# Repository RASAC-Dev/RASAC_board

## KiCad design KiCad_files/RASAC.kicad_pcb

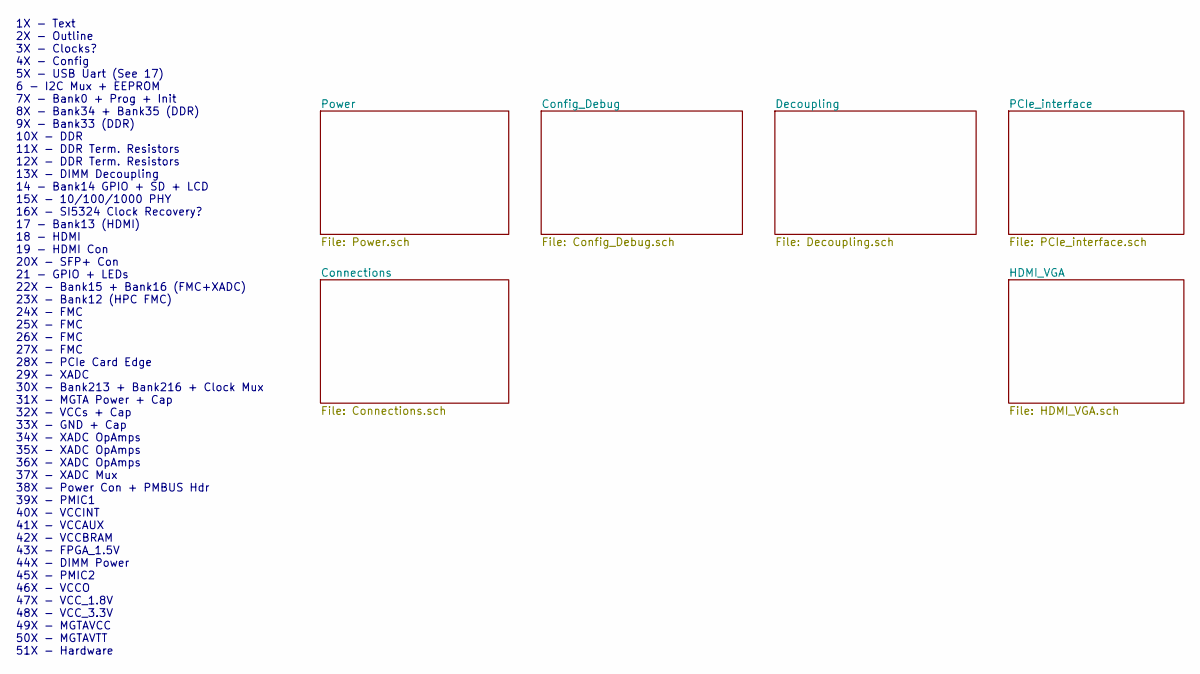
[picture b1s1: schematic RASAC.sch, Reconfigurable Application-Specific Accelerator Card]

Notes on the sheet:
1X - Text 2X - Outline 3X - Clocks? 4X - Config 5X - USB Uart (See 17) 6 - I2C Mux + EEPROM 7X - Bank0 + Prog + Init 8X - Bank34 + Bank35 (DDR) 9X - Bank33 (DDR) 10X - DDR 11X - DDR Term. Resistors 12X - DDR Term. Resistors 13X - DIMM Decoupling 14 - Bank14 GPIO + SD + LCD 15X - 10/100/1000 PHY 16X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

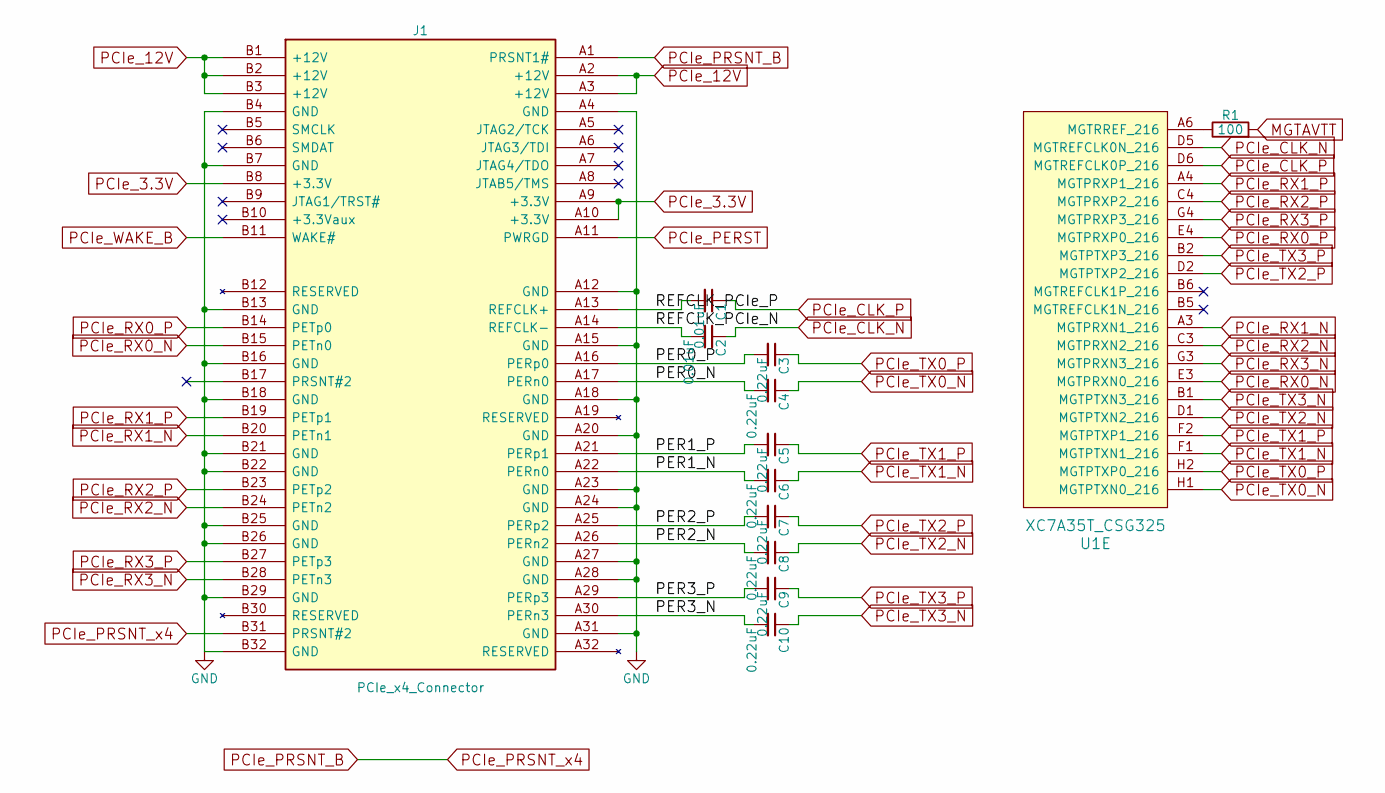
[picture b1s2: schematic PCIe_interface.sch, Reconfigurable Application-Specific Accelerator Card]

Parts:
C1, C2: 0.01uF; C_1206
C3, C4, C5, C6, C7, C8, C9, C10: 0.22uF; C_0805
J1: PCIe_x4_Connector; pciex4fingers
R1: 100; R_0603
U1: XC7A35T_CSG325; BGA-324_15.0x15.0mm_Layout18x18_P0.8mm_Ball0.5mm_Pad0.4mm_N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

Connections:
/PCIe_interface/PER0_N: C4.2, J1.A17 (PERn0)
/PCIe_interface/PER0_P: C3.2, J1.A16 (PERp0)
/PCIe_interface/PER1_N: C6.2, J1.A22 (PERn0)
/PCIe_interface/PER1_P: C5.2, J1.A21 (PERp1)
/PCIe_interface/PER2_N: C8.2, J1.A26 (PERn2)
/PCIe_interface/PER2_P: C7.2, J1.A25 (PERp2)
/PCIe_interface/PER3_N: C10.2, J1.A30 (PERn3)
/PCIe_interface/PER3_P: C9.2, J1.A29 (PERp3)
/PCIe_interface/REFCLK_PCIe_N: C2.2, J1.A14 (REFCLK-)
/PCIe_interface/REFCLK_PCIe_P: C1.2, J1.A13 (REFCLK+)
GND: J1.A4 (GND), J1.A12 (GND), J1.A15 (GND), J1.A18 (GND), J1.A20 (GND), J1.A23 (GND), J1.A24 (GND), J1.A27 (GND), J1.A28 (GND), J1.A31 (GND), J1.B4 (GND), J1.B7 (GND), J1.B13 (GND), J1.B16 (GND), J1.B18 (GND), J1.B21 (GND), J1.B22 (GND), J1.B25 (GND), J1.B26 (GND), J1.B29 (GND), J1.B32 (GND); also elsewhere on the board
MGTAVTT: R1.2; also elsewhere on the board
unnamed: R1.1, U1.A6 (MGTRREF_216)
PCIe_3.3V: J1.A9 (+3.3V), J1.A10 (+3.3V), J1.B8 (+3.3V); also elsewhere on the board
PCIe_12V: J1.A2 (+12V), J1.A3 (+12V), J1.B1 (+12V), J1.B2 (+12V), J1.B3 (+12V); also elsewhere on the board
PCIe_CLK_N: C2.1, U1.D5 (MGTREFCLK0N_216)
PCIe_CLK_P: C1.1, U1.D6 (MGTREFCLK0P_216)
PCIe_PERST: J1.A11 (PWRGD); also elsewhere on the board
PCIe_PRSNT_B: J1.A1 (PRSNT1#), J1.B31 (PRSNT#2)
PCIe_RX0_N: J1.B15 (PETn0), U1.E3 (MGTPRXN0_216)
PCIe_RX0_P: J1.B14 (PETp0), U1.E4 (MGTPRXP0_216)
PCIe_RX1_N: J1.B20 (PETn1), U1.A3 (MGTPRXN1_216)
PCIe_RX1_P: J1.B19 (PETp1), U1.A4 (MGTPRXP1_216)
PCIe_RX2_N: J1.B24 (PETn2), U1.C3 (MGTPRXN2_216)
PCIe_RX2_P: J1.B23 (PETp2), U1.C4 (MGTPRXP2_216)
PCIe_RX3_N: J1.B28 (PETn3), U1.G3 (MGTPRXN3_216)
PCIe_RX3_P: J1.B27 (PETp3), U1.G4 (MGTPRXP3_216)
PCIe_TX0_N: C4.1, U1.H1 (MGTPTXN0_216)
PCIe_TX0_P: C3.1, U1.H2 (MGTPTXP0_216)
PCIe_TX1_N: C6.1, U1.F1 (MGTPTXN1_216)
PCIe_TX1_P: C5.1, U1.F2 (MGTPTXP1_216)
PCIe_TX2_N: C8.1, U1.D1 (MGTPTXN2_216)
PCIe_TX2_P: C7.1, U1.D2 (MGTPTXP2_216)
PCIe_TX3_N: C10.1, U1.B1 (MGTPTXN3_216)
PCIe_TX3_P: C9.1, U1.B2 (MGTPTXP3_216)
PCIe_WAKE_B: J1.B11 (WAKE#); also elsewhere on the board

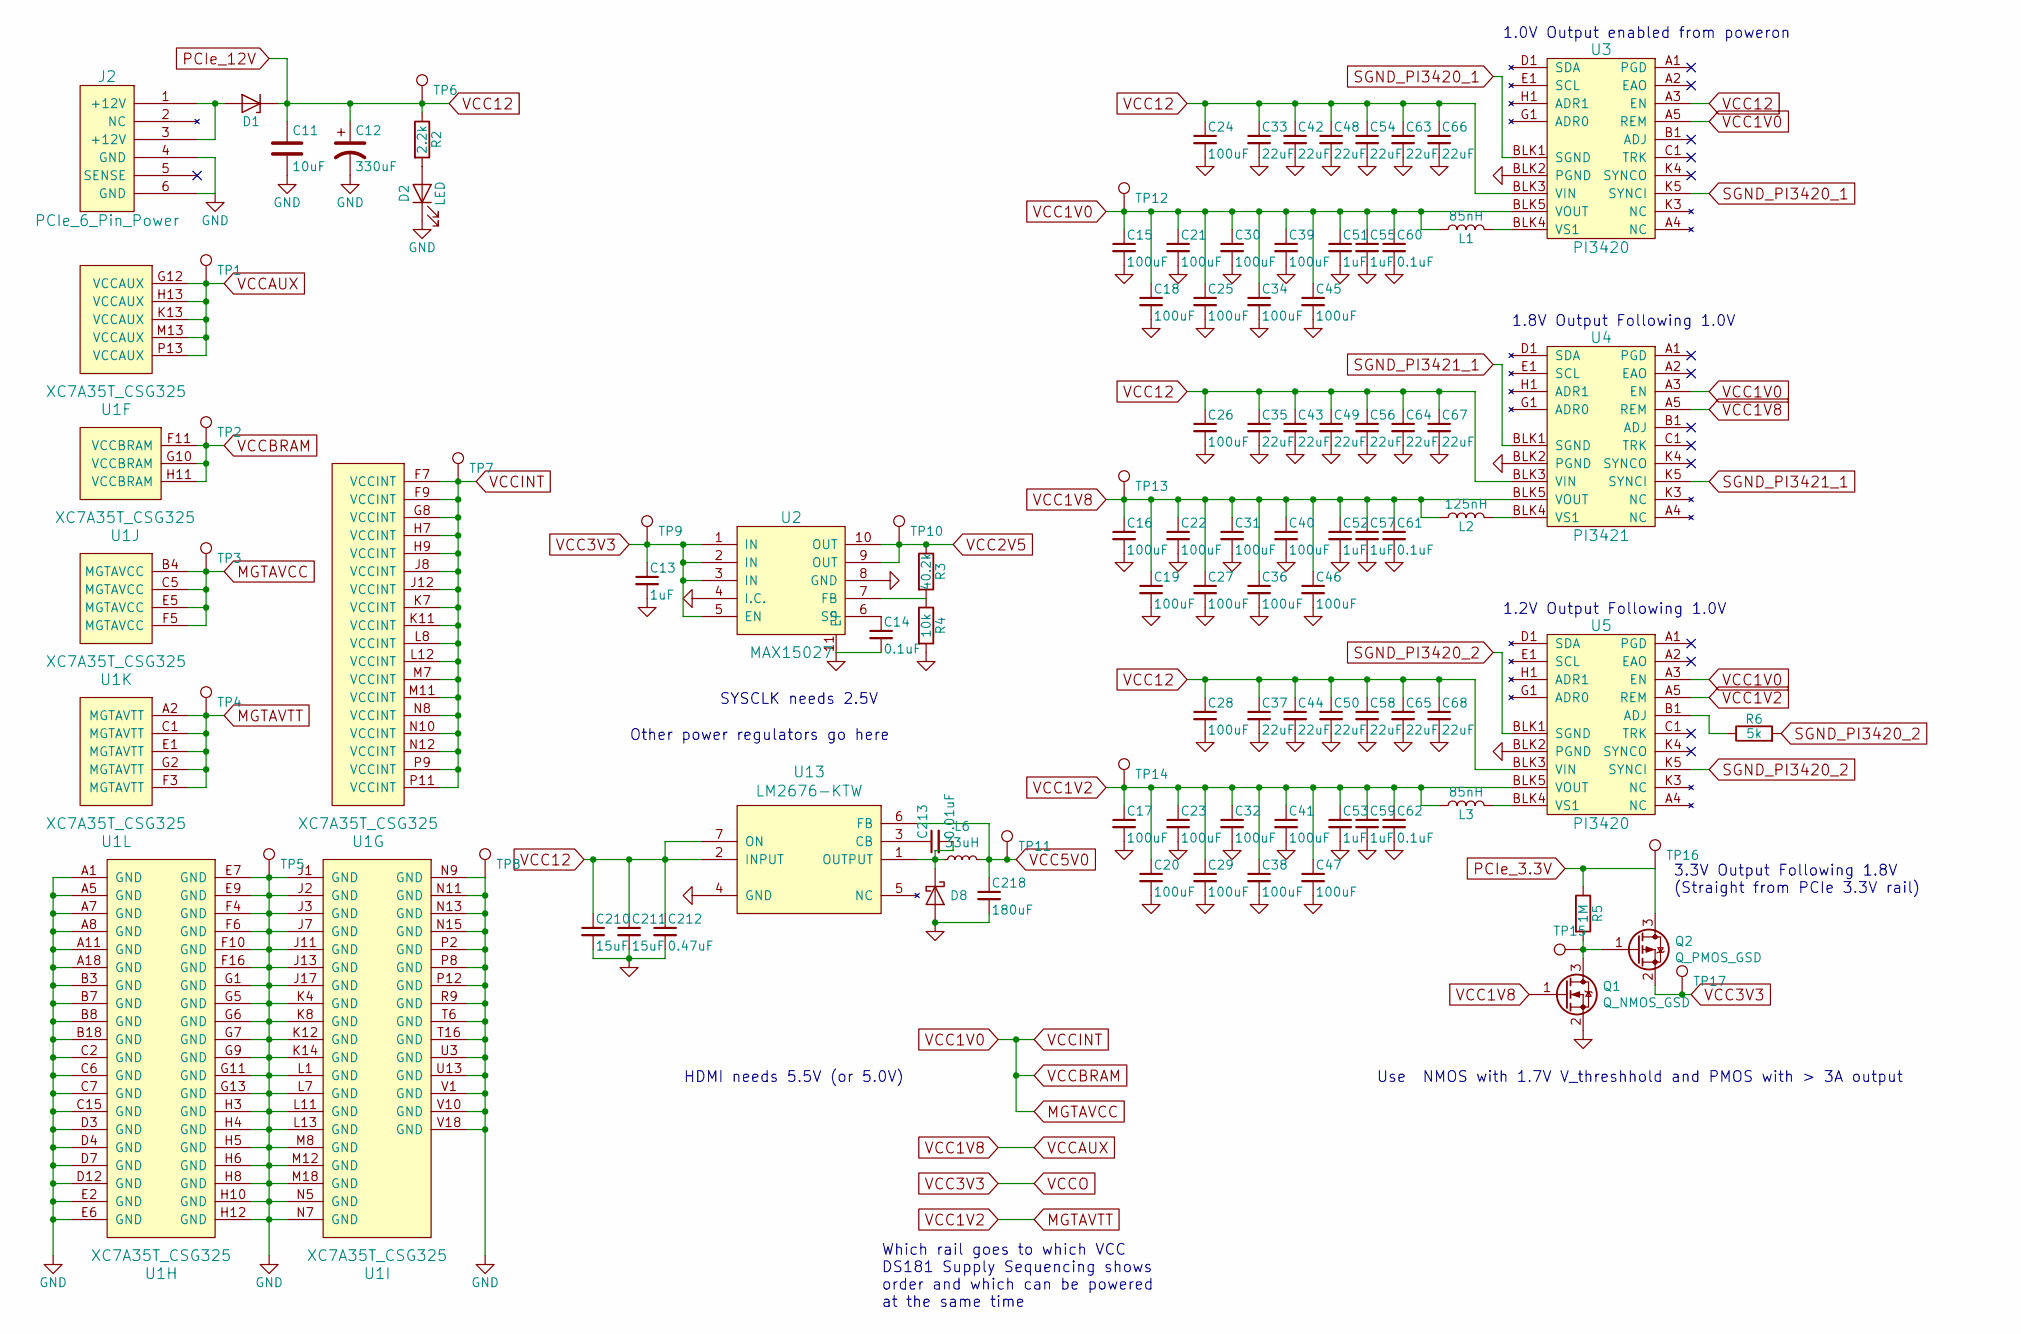
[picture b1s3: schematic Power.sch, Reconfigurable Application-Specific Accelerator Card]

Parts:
C11: 10uF; C_0805
C12: 330uF; C_1210
C13, C51, C52, C53, C55, C57, C59: 1uF; C_0805
C14: 0.1uF; C_0402
C15, C16, C17, C18, C19, C20, C21, C22, C23, C24, C25, C26, C27, C28, C29, C30, C31, C32, C34, C36, C38, C39, C40, C41, C45, C46, C47: 100uF; C_1210
C33, C35, C37, C42, C43, C44, C48, C49, C50, C54, C56, C58, C63, C64, C65, C66, C67, C68: 22uF; C_0805
C60, C61, C62: 0.1uF; C_0805
C210, C211: 15uF; C_1210
C212: 0.47uF; C_0805
C213: 0.01uF; C_1206
C218: 180uF; C_1206
D1: D_Zener; D_SOD-123
D2: LED; LED_0603
D8: D_Schottky; D_SOD-123
J2: PCIe_6_Pin_Power; Molex_MiniFit-JR-5569-06A2_2x03x4.20mm_Angled
L1, L3: 85nH; L_1210
L2: 125nH; L_1210
L6: 33uH; L_0805
Q1: Q_NMOS_GSD; SOT-23
Q2: Q_PMOS_GSD; SOT-23
R2: 2.2k; R_0805
R3: 40.2k; R_0402
R4: 10k; R_0805
R5: 1M; R_0603
R6: 5k; R_0805
TP1, TP2, TP3, TP4, TP5, TP6, TP7, TP8, TP9, TP10, TP11, TP12, TP13, TP14, TP15, TP16, TP17: TestPoint; Measurement_Point_Round-SMD-Pad_Small
U1: XC7A35T_CSG325; BGA-324_15.0x15.0mm_Layout18x18_P0.8mm_Ball0.5mm_Pad0.4mm_N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
U2: MAX15027; TDFN-10_3x3mm_Pitch0.5mm
U3, U5: PI3420; LGA-123_10x14mm_Pitch1.0mm
U4: PI3421; LGA-123_10x14mm_Pitch1.0mm
U13: LM2676-KTW; TO-263-7_TabPin4

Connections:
GND: C11.2, C12.2, C13.2, C14.2, C15.2, C16.2, C17.2, C18.2, C19.2, C20.2, C21.2, C22.2, C23.2, C24.2, C25.2, C26.2, C27.2, C28.2, C29.2, C30.2, C31.2, C32.2, C33.2, C34.2, C35.2, C36.2, C37.2, C38.2, C39.2, C40.2, C41.2, C42.2, C43.2, C44.2, C45.2, C46.2, C47.2, C48.2, C49.2, C50.2, C51.2, C52.2, C53.2, C54.2, C55.2, C56.2, C57.2, C58.2, C59.2, C60.2, C61.2, C62.2, C63.2, C64.2, C65.2, C66.2, C67.2, C68.2, C210.2, C211.2, C212.2, C218.2, D2.1 (K), D8.2 (A), J2.4 (GND), J2.6 (GND), Q1.2 (S), R4.2, TP5.1, TP8.1, U1.A1 (GND), U1.A5 (GND), U1.A7 (GND), U1.A8 (GND), U1.A11 (GND), U1.A18 (GND), U1.B3 (GND), U1.B7 (GND), U1.B8 (GND), U1.B18 (GND), U1.C2 (GND), U1.C6 (GND), U1.C7 (GND), U1.C15 (GND), U1.D3 (GND), U1.D4 (GND), U1.D7 (GND), U1.D12 (GND), U1.E2 (GND), U1.E6 (GND), U1.E7 (GND), U1.E9 (GND), U1.F4 (GND), U1.F6 (GND), U1.F10 (GND), U1.F16 (GND), U1.G1 (GND), U1.G5 (GND), U1.G6 (GND), U1.G7 (GND), U1.G9 (GND), U1.G11 (GND), U1.G13 (GND), U1.H3 (GND), U1.H4 (GND), U1.H5 (GND), U1.H6 (GND), U1.H8 (GND), U1.H10 (GND), U1.H12 (GND), U1.J1 (GND), U1.J2 (GND), U1.J3 (GND), U1.J7 (GND), U1.J11 (GND), U1.J13 (GND), U1.J17 (GND), U1.K4 (GND), U1.K8 (GND), U1.K12 (GND), U1.K14 (GND), U1.L1 (GND), U1.L7 (GND), U1.L11 (GND), U1.L13 (GND), U1.M8 (GND), U1.M12 (GND), U1.M18 (GND), U1.N5 (GND), U1.N7 (GND), U1.N9 (GND), U1.N11 (GND), U1.N13 (GND), U1.N15 (GND), U1.P2 (GND), U1.P8 (GND), U1.P12 (GND), U1.R9 (GND), U1.T6 (GND), U1.T16 (GND), U1.U3 (GND), U1.U13 (GND), U1.V1 (GND), U1.V10 (GND), U1.V18 (GND), U2.4 (I.C.), U2.8 (GND), U2.11 (EP), U3.BLK2 (PGND), U4.BLK2 (PGND), U5.BLK2 (PGND), U13.4 (GND); also elsewhere on the board
MGTAVCC: C15.1, C18.1, C21.1, C25.1, C30.1, C34.1, C39.1, C45.1, C51.1, C55.1, C60.1, L1.1, TP2.1, TP3.1, TP7.1, TP12.1, U1.B4 (MGTAVCC), U1.C5 (MGTAVCC), U1.E5 (MGTAVCC), U1.F5 (MGTAVCC), U1.F7 (VCCINT), U1.F9 (VCCINT), U1.F11 (VCCBRAM), U1.G8 (VCCINT), U1.G10 (VCCBRAM), U1.H7 (VCCINT), U1.H9 (VCCINT), U1.H11 (VCCBRAM), U1.J8 (VCCINT), U1.J12 (VCCINT), U1.K7 (VCCINT), U1.K11 (VCCINT), U1.L8 (VCCINT), U1.L12 (VCCINT), U1.M7 (VCCINT), U1.M11 (VCCINT), U1.N8 (VCCINT), U1.N10 (VCCINT), U1.N12 (VCCINT), U1.P9 (VCCINT), U1.P11 (VCCINT), U3.A5 (REM), U3.BLK5 (VOUT), U4.A3 (EN), U5.A3 (EN); also elsewhere on the board
MGTAVTT: C17.1, C20.1, C23.1, C29.1, C32.1, C38.1, C41.1, C47.1, C53.1, C59.1, C62.1, L3.1, TP4.1, TP14.1, U1.A2 (MGTAVTT), U1.C1 (MGTAVTT), U1.E1 (MGTAVTT), U1.F3 (MGTAVTT), U1.G2 (MGTAVTT), U5.A5 (REM), U5.BLK5 (VOUT); also elsewhere on the board
unnamed: C14.1, U2.6 (SS)
unnamed: C213.1, U13.3 (CB)
unnamed: C213.2, D8.1 (K), L6.1, U13.1 (OUTPUT)
unnamed: D1.2 (A), J2.1 (+12V), J2.3 (+12V)
unnamed: D2.2 (A), R2.2
unnamed: L1.2, U3.BLK4 (VS1)
unnamed: L2.2, U4.BLK4 (VS1)
unnamed: L3.2, U5.BLK4 (VS1)
unnamed: Q1.3 (D), Q2.1 (G), R5.2, TP15.1
unnamed: R3.2, R4.1, U2.7 (FB)
unnamed: R6.1, U5.B1 (ADJ)
PCIe_3.3V: Q2.3 (D), R5.1, TP16.1; also elsewhere on the board
PCIe_12V: C11.1, C12.1, C24.1, C26.1, C28.1, C33.1, C35.1, C37.1, C42.1, C43.1, C44.1, C48.1, C49.1, C50.1, C54.1, C56.1, C58.1, C63.1, C64.1, C65.1, C66.1, C67.1, C68.1, C210.1, C211.1, C212.1, D1.1 (K), R2.1, TP6.1, U3.A3 (EN), U3.BLK3 (VIN), U4.BLK3 (VIN), U5.BLK3 (VIN), U13.2 (INPUT), U13.7 (ON); also elsewhere on the board
SGND_PI3420_1: U3.BLK1 (SGND), U3.K5 (SYNCI)
SGND_PI3420_2: R6.2, U5.BLK1 (SGND), U5.K5 (SYNCI)
SGND_PI3421_1: U4.BLK1 (SGND), U4.K5 (SYNCI)
VCC1V8: C16.1, C19.1, C22.1, C27.1, C31.1, C36.1, C40.1, C46.1, C52.1, C57.1, C61.1, L2.1, Q1.1 (G), TP1.1, TP13.1, U1.G12 (VCCAUX), U1.H13 (VCCAUX), U1.K13 (VCCAUX), U1.M13 (VCCAUX), U1.P13 (VCCAUX), U4.A5 (REM), U4.BLK5 (VOUT); also elsewhere on the board
VCC2V5: R3.1, TP10.1, U2.9 (OUT), U2.10 (OUT); also elsewhere on the board
VCC3V3: C13.1, Q2.2 (S), TP9.1, TP17.1, U2.1 (IN), U2.2 (IN), U2.3 (IN), U2.5 (EN); also elsewhere on the board
VCC5V0: C218.1, L6.2, TP11.1, U13.6 (FB); also elsewhere on the board

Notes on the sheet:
Use NMOS with 1.7V V_threshhold and PMOS with > 3A output
Other power regulators go here
1.2V Output Following 1.0V
1.8V Output Following 1.0V
1.0V Output enabled from poweron
3.3V Output Following 1.8V (Straight from PCIe 3.3V rail)
Which rail goes to which VCC DS181 Supply Sequencing shows order and which can be powered at the same time
SYSCLK needs 2.5V
HDMI needs 5.5V (or 5.0V)

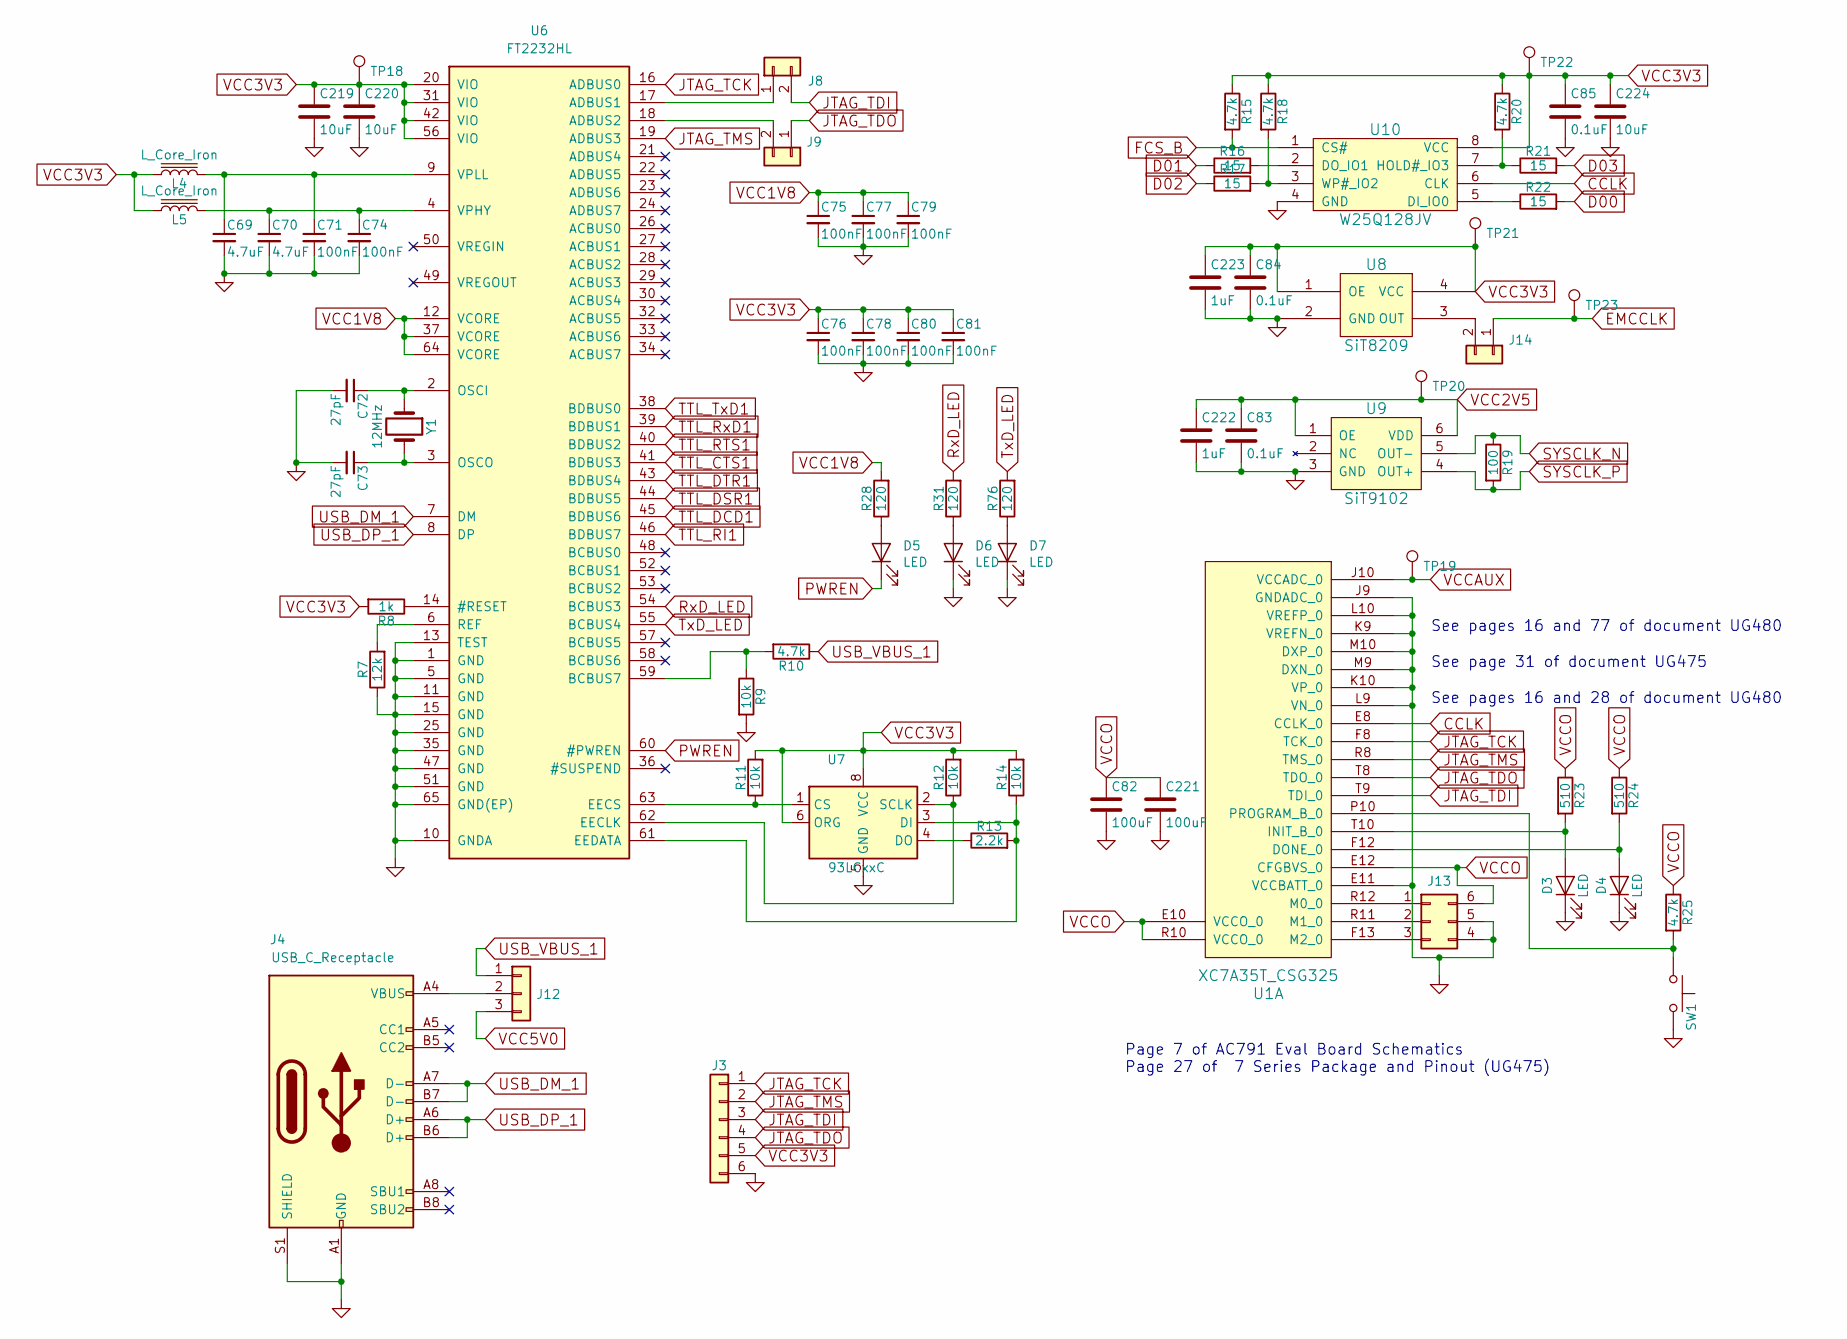
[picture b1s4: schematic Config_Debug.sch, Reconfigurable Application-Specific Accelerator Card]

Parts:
C69, C70: 4.7uF; C_0603
C71, C74, C75, C76, C77, C78, C79, C80, C81: 100nF; C_0805
C72, C73: 27pF; C_0805
C82: 100uF; C_0805
C83, C84, C85: 0.1uF; C_0805
C219, C220, C224: 10uF; C_0805
C221: 100uF; C_1210
C222, C223: 1uF; C_0805
D3, D4, D5, D6, D7: LED; LED_0603
J3: Conn_01x06; Pin_Header_Straight_2x03_Pitch2.54mm
J4: USB_C_Receptacle; USB_C_Receptacle_Amphenol_12401610E4-2A
J8, J9, J14: Conn_01x02; Pin_Header_Straight_1x02_Pitch2.54mm
J12: Conn_01x03; Pin_Header_Straight_1x03_Pitch2.54mm
J13: Conn_02x03_Counter_Clockwise; Pin_Header_Straight_2x03_Pitch2.54mm_SMD
L4, L5: L_Core_Iron; L_0805
R7: 12k; R_0402
R8: 1k; R_0805
R9, R11, R12, R14: 10k; R_0805
R10, R15, R18, R20, R25: 4.7k; R_0805
R13: 2.2k; R_0805
R16, R17, R21, R22: 15; R_0805
R19: 100; R_0603
R23, R24: 510; R_0805
R28, R31, R76: 120; R_0805
SW1: SW_Push; SW_SPST_PTS645
TP18, TP19, TP20, TP21, TP22, TP23: TestPoint; Measurement_Point_Round-SMD-Pad_Small
U1: XC7A35T_CSG325; BGA-324_15.0x15.0mm_Layout18x18_P0.8mm_Ball0.5mm_Pad0.4mm_N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
U6: FT2232HL; LQFP-64-1EP_10x10mm_Pitch0.5mm; MPN FT2232HL
U7: 93LCxxC; SOIC-8-N
U8: SiT8209; 4-SMD
U9: SiT9102; 6-SMD
U10: W25Q128JV; SOIC-8-N
Y1: 12MHz; Crystal_SMD_HC49-SD

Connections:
CCLK: U1.E8 (CCLK_0), U10.6 (CLK)
D00: R22.2; also elsewhere on the board
D01: R16.1; also elsewhere on the board
D02: R17.1; also elsewhere on the board
D03: R21.2; also elsewhere on the board
EMCCLK: J14.1, TP23.1; also elsewhere on the board
FCS_B: R15.2, U10.1 (CS#); also elsewhere on the board
GND: C69.2, C70.2, C71.2, C72.2, C73.2, C74.2, C75.2, C76.2, C77.2, C78.2, C79.2, C80.2, C81.2, C82.2, C83.2, C84.2, C85.2, C219.2, C220.2, C221.2, C222.2, C223.2, C224.2, D3.1 (K), D4.1 (K), D6.1 (K), D7.1 (K), J3.6, J4.A1 (GND), J4.A12 (GND), J4.B1 (GND), J4.B12 (GND), J4.S1 (SHIELD), J13.4, J13.5, R7.1, R9.2, SW1.2, U1.E11 (VCCBATT_0), U1.J9 (GNDADC_0), U1.K9 (VREFN_0), U1.K10 (VP_0), U1.L9 (VN_0), U1.L10 (VREFP_0), U1.M9 (DXN_0), U1.M10 (DXP_0), U6.1 (GND), U6.5 (GND), U6.10 (GNDA), U6.11 (GND), U6.13 (TEST), U6.15 (GND), U6.25 (GND), U6.35 (GND), U6.47 (GND), U6.51 (GND), U6.65 (GND(EP)), U7.5 (GND), U8.2 (GND), U9.3 (GND), U10.4 (GND); also elsewhere on the board
JTAG_TCK: J3.1, U1.F8 (TCK_0), U6.16 (ADBUS0)
JTAG_TDI: J3.3, J8.2, U1.T9 (TDI_0)
JTAG_TDO: J3.4, J9.1, U1.T8 (TDO_0)
JTAG_TMS: J3.2, U1.R8 (TMS_0), U6.19 (ADBUS3)
unnamed: C69.1, C71.1, L4.2, U6.9 (VPLL)
unnamed: C70.1, C74.1, L5.2, U6.4 (VPHY)
unnamed: C72.1, U6.2 (OSCI), Y1.1
unnamed: C73.1, U6.3 (OSCO), Y1.2
unnamed: D3.2 (A), R23.2, U1.T10 (INIT_B_0)
unnamed: D4.2 (A), R24.2, U1.F12 (DONE_0)
unnamed: D5.2 (A), R28.1
unnamed: D6.2 (A), R31.1
unnamed: D7.2 (A), R76.1
unnamed: J8.1, U6.17 (ADBUS1)
unnamed: J9.2, U6.18 (ADBUS2)
unnamed: J4.A4 (VBUS), J4.A9 (VBUS), J4.B4 (VBUS), J4.B9 (VBUS), J12.2
unnamed: J13.1, U1.R12 (M0_0)
unnamed: J13.2, U1.R11 (M1_0)
unnamed: J13.3, U1.F13 (M2_0)
unnamed: J14.2, U8.3 (OUT)
unnamed: R7.2, U6.6 (REF)
unnamed: R8.1, U6.14 (#RESET)
unnamed: R9.1, R10.2, U6.59 (BCBUS7)
unnamed: R11.1, U6.63 (EECS), U7.1 (CS)
unnamed: R12.1, U6.62 (EECLK), U7.2 (SCLK)
unnamed: R13.1, U7.4 (DO)
unnamed: R13.2, R14.1, U6.61 (EEDATA), U7.3 (DI)
unnamed: R16.2, U10.2 (DO_IO1)
unnamed: R17.2, R18.2, U10.3 (WP#_IO2)
unnamed: R20.2, R21.1, U10.7 (HOLD#_IO3)
unnamed: R22.1, U10.5 (DI_IO0)
unnamed: R25.2, SW1.1, U1.P10 (PROGRAM_B_0)
PWREN: D5.1 (K), U6.60 (#PWREN)
RxD_LED: R31.2, U6.54 (BCBUS3)
SYSCLK_N: R19.1, U9.5 (OUT-); also elsewhere on the board
SYSCLK_P: R19.2, U9.4 (OUT+); also elsewhere on the board
TTL_CTS1: U6.41 (BDBUS3); also elsewhere on the board
TTL_DCD1: U6.45 (BDBUS6); also elsewhere on the board
TTL_DSR1: U6.44 (BDBUS5); also elsewhere on the board
TTL_DTR1: U6.43 (BDBUS4); also elsewhere on the board
TTL_RI1: U6.46 (BDBUS7); also elsewhere on the board
TTL_RTS1: U6.40 (BDBUS2); also elsewhere on the board
TTL_RxD1: U6.39 (BDBUS1); also elsewhere on the board
TTL_TxD1: U6.38 (BDBUS0); also elsewhere on the board
TxD_LED: R76.2, U6.55 (BCBUS4)
USB_DM_1: J4.A7 (D-), J4.B7 (D-), U6.7 (DM)
USB_DP_1: J4.A6 (D+), J4.B6 (D+), U6.8 (DP)
USB_VBUS_1: J12.1, R10.1
VCC1V8: C75.1, C77.1, C79.1, R28.2, TP19.1, U1.J10 (VCCADC_0), U6.12 (VCORE), U6.37 (VCORE), U6.64 (VCORE); also elsewhere on the board
VCC2V5: C83.1, C222.1, TP20.1, U9.1 (OE), U9.6 (VDD); also elsewhere on the board
VCC3V3: C76.1, C78.1, C80.1, C81.1, C82.1, C84.1, C85.1, C219.1, C220.1, C221.1, C223.1, C224.1, J3.5, J13.6, L4.1, L5.1, R8.2, R11.2, R12.2, R14.2, R15.1, R18.1, R20.1, R23.1, R24.1, R25.1, TP18.1, TP21.1, TP22.1, U1.E10 (VCCO_0), U1.E12 (CFGBVS_0), U1.R10 (VCCO_0), U6.20 (VIO), U6.31 (VIO), U6.42 (VIO), U6.56 (VIO), U7.6 (ORG), U7.8 (VCC), U8.1 (OE), U8.4 (VCC), U10.8 (VCC); also elsewhere on the board
VCC5V0: J12.3; also elsewhere on the board

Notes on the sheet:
Page 7 of AC791 Eval Board Schematics Page 27 of 7 Series Package and Pinout (UG475)
See pages 16 and 77 of document UG480
See pages 16 and 28 of document UG480
See page 31 of document UG475

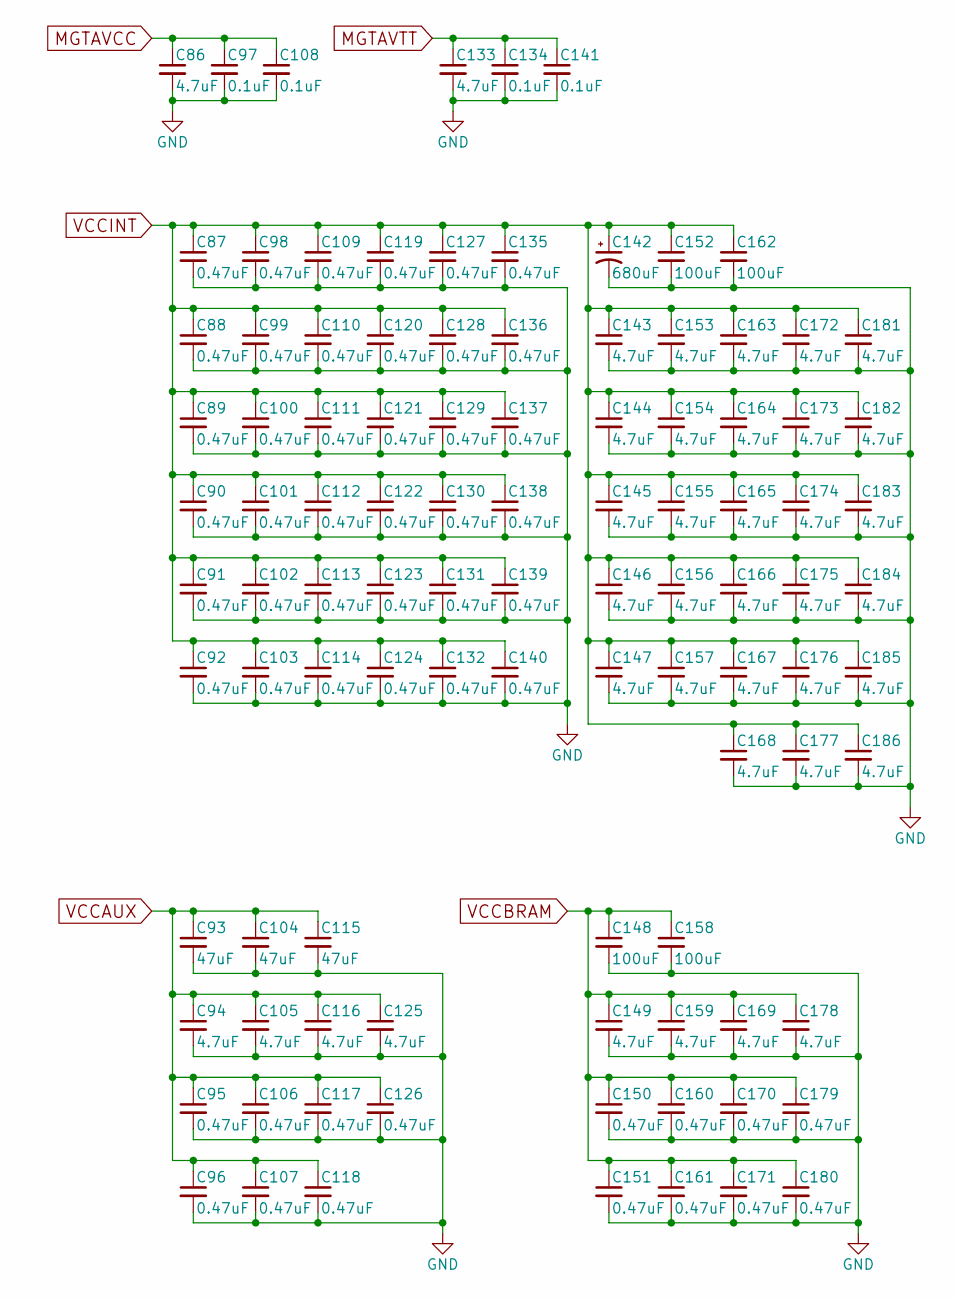
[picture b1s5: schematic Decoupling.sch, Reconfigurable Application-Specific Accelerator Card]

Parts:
C86, C94, C105, C116, C125, C133, C143, C144, C145, C146, C147, C149, C153, C154, C155, C156, C157, C159, C163, C164, C165, C166, C167, C168, C169, C172, C173, C174, C175, C176, C177, C178, C181, C182, C183, C184, C185, C186: 4.7uF; C_0603
C87, C88, C89, C90, C91, C92, C95, C96, C98, C99, C100, C101, C102, C103, C106, C107, C109, C110, C111, C112, C113, C114, C117, C118, C119, C120, C121, C122, C123, C124, C126, C127, C128, C129, C130, C131, C132, C135, C136, C137, C138, C139, C140, C150, C151, C160, C161, C170, C171, C179, C180: 0.47uF; C_0805
C93, C104, C115: 47uF; C_0805
C97, C108, C134, C141: 0.1uF; C_0805
C142: 680uF; CP_Tantalum_Case-D_EIA-7343-31_Wave
C148, C152, C158, C162: 100uF; C_1210

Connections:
GND: C86.2, C87.2, C88.2, C89.2, C90.2, C91.2, C92.2, C93.2, C94.2, C95.2, C96.2, C97.2, C98.2, C99.2, C100.2, C101.2, C102.2, C103.2, C104.2, C105.2, C106.2, C107.2, C108.2, C109.2, C110.2, C111.2, C112.2, C113.2, C114.2, C115.2, C116.2, C117.2, C118.2, C119.2, C120.2, C121.2, C122.2, C123.2, C124.2, C125.2, C126.2, C127.2, C128.2, C129.2, C130.2, C131.2, C132.2, C133.2, C134.2, C135.2, C136.2, C137.2, C138.2, C139.2, C140.2, C141.2, C142.2, C143.2, C144.2, C145.2, C146.2, C147.2, C148.2, C149.2, C150.2, C151.2, C152.2, C153.2, C154.2, C155.2, C156.2, C157.2, C158.2, C159.2, C160.2, C161.2, C162.2, C163.2, C164.2, C165.2, C166.2, C167.2, C168.2, C169.2, C170.2, C171.2, C172.2, C173.2, C174.2, C175.2, C176.2, C177.2, C178.2, C179.2, C180.2, C181.2, C182.2, C183.2, C184.2, C185.2, C186.2; also elsewhere on the board
MGTAVCC: C86.1, C87.1, C88.1, C89.1, C90.1, C91.1, C92.1, C97.1, C98.1, C99.1, C100.1, C101.1, C102.1, C103.1, C108.1, C109.1, C110.1, C111.1, C112.1, C113.1, C114.1, C119.1, C120.1, C121.1, C122.1, C123.1, C124.1, C127.1, C128.1, C129.1, C130.1, C131.1, C132.1, C135.1, C136.1, C137.1, C138.1, C139.1, C140.1, C142.1, C143.1, C144.1, C145.1, C146.1, C147.1, C148.1, C149.1, C150.1, C151.1, C152.1, C153.1, C154.1, C155.1, C156.1, C157.1, C158.1, C159.1, C160.1, C161.1, C162.1, C163.1, C164.1, C165.1, C166.1, C167.1, C168.1, C169.1, C170.1, C171.1, C172.1, C173.1, C174.1, C175.1, C176.1, C177.1, C178.1, C179.1, C180.1, C181.1, C182.1, C183.1, C184.1, C185.1, C186.1; also elsewhere on the board
MGTAVTT: C133.1, C134.1, C141.1; also elsewhere on the board
VCC1V8: C93.1, C94.1, C95.1, C96.1, C104.1, C105.1, C106.1, C107.1, C115.1, C116.1, C117.1, C118.1, C125.1, C126.1; also elsewhere on the board

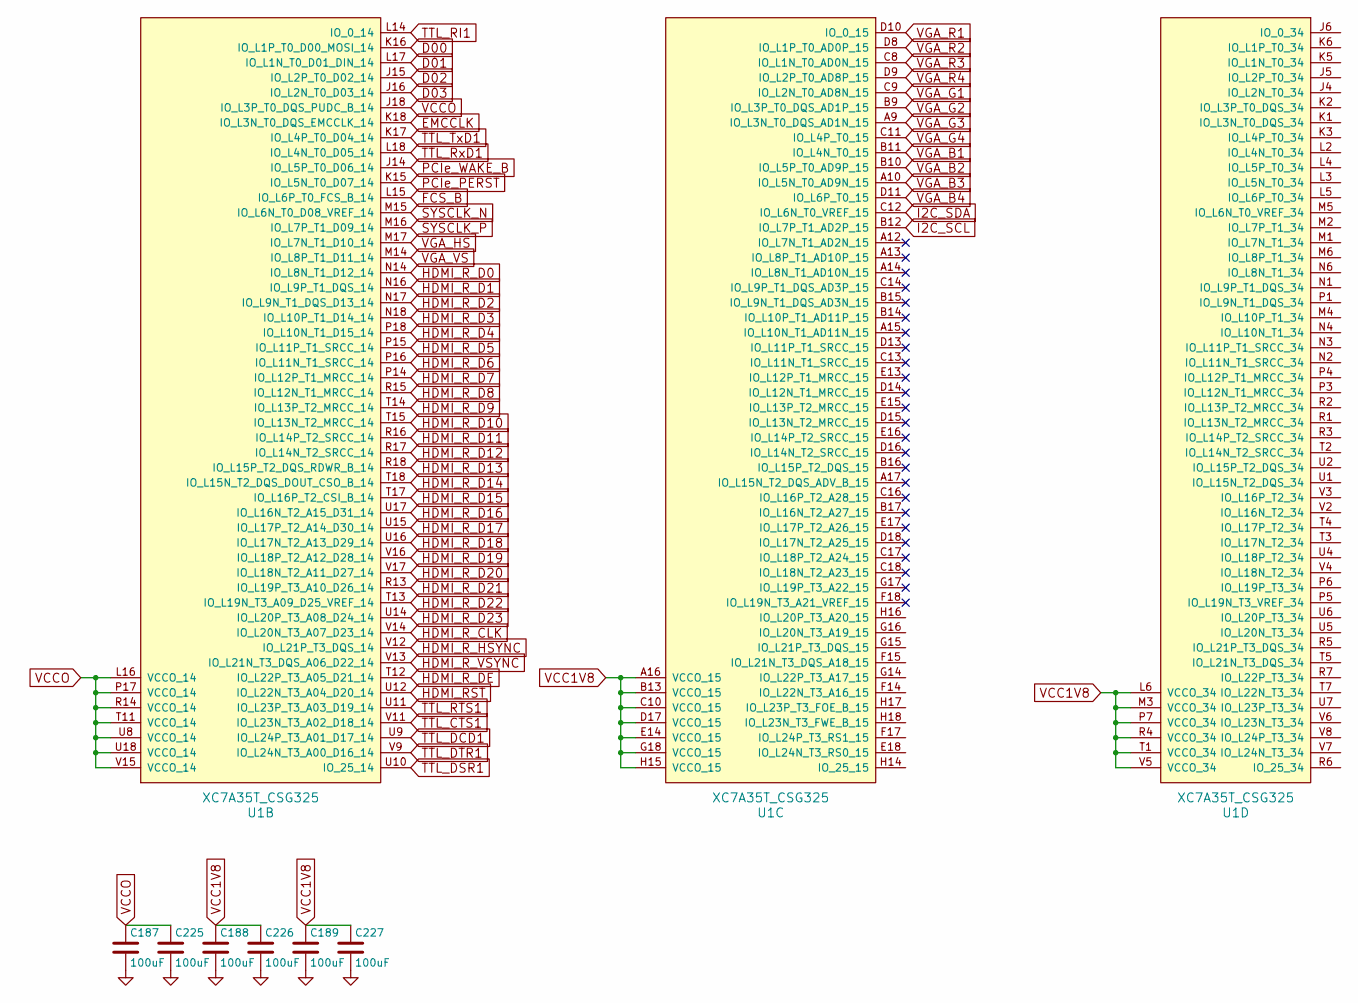
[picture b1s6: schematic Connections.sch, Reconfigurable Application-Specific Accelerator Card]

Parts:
C187, C188, C189, C225, C226, C227: 100uF; C_1210
U1: XC7A35T_CSG325; BGA-324_15.0x15.0mm_Layout18x18_P0.8mm_Ball0.5mm_Pad0.4mm_N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

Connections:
D00: U1.K16 (IO_L1P_T0_D00_MOSI_14); also elsewhere on the board
D01: U1.L17 (IO_L1N_T0_D01_DIN_14); also elsewhere on the board
D02: U1.J15 (IO_L2P_T0_D02_14); also elsewhere on the board
D03: U1.J16 (IO_L2N_T0_D03_14); also elsewhere on the board
EMCCLK: U1.K18 (IO_L3N_T0_DQS_EMCCLK_14); also elsewhere on the board
FCS_B: U1.L15 (IO_L6P_T0_FCS_B_14); also elsewhere on the board
GND: C187.2, C188.2, C189.2, C225.2, C226.2, C227.2; also elsewhere on the board
HDMI_RST: U1.U12 (IO_L22N_T3_A04_D20_14); also elsewhere on the board
HDMI_R_CLK: U1.V14 (IO_L20N_T3_A07_D23_14); also elsewhere on the board
HDMI_R_D0: U1.N14 (IO_L8N_T1_D12_14); also elsewhere on the board
HDMI_R_D1: U1.N16 (IO_L9P_T1_DQS_14); also elsewhere on the board
HDMI_R_D2: U1.N17 (IO_L9N_T1_DQS_D13_14); also elsewhere on the board
HDMI_R_D3: U1.N18 (IO_L10P_T1_D14_14); also elsewhere on the board
HDMI_R_D4: U1.P18 (IO_L10N_T1_D15_14); also elsewhere on the board
HDMI_R_D5: U1.P15 (IO_L11P_T1_SRCC_14); also elsewhere on the board
HDMI_R_D6: U1.P16 (IO_L11N_T1_SRCC_14); also elsewhere on the board
HDMI_R_D7: U1.P14 (IO_L12P_T1_MRCC_14); also elsewhere on the board
HDMI_R_D8: U1.R15 (IO_L12N_T1_MRCC_14); also elsewhere on the board
HDMI_R_D9: U1.T14 (IO_L13P_T2_MRCC_14); also elsewhere on the board
HDMI_R_D10: U1.T15 (IO_L13N_T2_MRCC_14); also elsewhere on the board
HDMI_R_D11: U1.R16 (IO_L14P_T2_SRCC_14); also elsewhere on the board
HDMI_R_D12: U1.R17 (IO_L14N_T2_SRCC_14); also elsewhere on the board
HDMI_R_D13: U1.R18 (IO_L15P_T2_DQS_RDWR_B_14); also elsewhere on the board
HDMI_R_D14: U1.T18 (IO_L15N_T2_DQS_DOUT_CSO_B_14); also elsewhere on the board
HDMI_R_D15: U1.T17 (IO_L16P_T2_CSI_B_14); also elsewhere on the board
HDMI_R_D16: U1.U17 (IO_L16N_T2_A15_D31_14); also elsewhere on the board
HDMI_R_D17: U1.U15 (IO_L17P_T2_A14_D30_14); also elsewhere on the board
HDMI_R_D18: U1.U16 (IO_L17N_T2_A13_D29_14); also elsewhere on the board
HDMI_R_D19: U1.V16 (IO_L18P_T2_A12_D28_14); also elsewhere on the board
HDMI_R_D20: U1.V17 (IO_L18N_T2_A11_D27_14); also elsewhere on the board
HDMI_R_D21: U1.R13 (IO_L19P_T3_A10_D26_14); also elsewhere on the board
HDMI_R_D22: U1.T13 (IO_L19N_T3_A09_D25_VREF_14); also elsewhere on the board
HDMI_R_D23: U1.U14 (IO_L20P_T3_A08_D24_14); also elsewhere on the board
HDMI_R_DE: U1.T12 (IO_L22P_T3_A05_D21_14); also elsewhere on the board
HDMI_R_HSYNC: U1.V12 (IO_L21P_T3_DQS_14); also elsewhere on the board
HDMI_R_VSYNC: U1.V13 (IO_L21N_T3_DQS_A06_D22_14); also elsewhere on the board
HDMI_SCL: U1.B12 (IO_L7P_T1_AD2P_15); also elsewhere on the board
HDMI_SDA: U1.C12 (IO_L6N_T0_VREF_15); also elsewhere on the board
PCIe_PERST: U1.K15 (IO_L5N_T0_D07_14); also elsewhere on the board
PCIe_WAKE_B: U1.J14 (IO_L5P_T0_D06_14); also elsewhere on the board
SYSCLK_N: U1.M15 (IO_L6N_T0_D08_VREF_14); also elsewhere on the board
SYSCLK_P: U1.M16 (IO_L7P_T1_D09_14); also elsewhere on the board
TTL_CTS1: U1.V11 (IO_L23N_T3_A02_D18_14); also elsewhere on the board
TTL_DCD1: U1.U9 (IO_L24P_T3_A01_D17_14); also elsewhere on the board
TTL_DSR1: U1.U10 (IO_25_14); also elsewhere on the board
TTL_DTR1: U1.V9 (IO_L24N_T3_A00_D16_14); also elsewhere on the board
TTL_RI1: U1.L14 (IO_0_14); also elsewhere on the board
TTL_RTS1: U1.U11 (IO_L23P_T3_A03_D19_14); also elsewhere on the board
TTL_RxD1: U1.L18 (IO_L4N_T0_D05_14); also elsewhere on the board
TTL_TxD1: U1.K17 (IO_L4P_T0_D04_14); also elsewhere on the board
VCC1V8: C188.1, C189.1, C226.1, C227.1, U1.A16 (VCCO_15), U1.B13 (VCCO_15), U1.C10 (VCCO_15), U1.D17 (VCCO_15), U1.E14 (VCCO_15), U1.G18 (VCCO_15), U1.H15 (VCCO_15), U1.L6 (VCCO_34), U1.M3 (VCCO_34), U1.P7 (VCCO_34), U1.R4 (VCCO_34), U1.T1 (VCCO_34), U1.V5 (VCCO_34); also elsewhere on the board
VCC3V3: C187.1, C225.1, U1.J18 (IO_L3P_T0_DQS_PUDC_B_14), U1.L16 (VCCO_14), U1.P17 (VCCO_14), U1.R14 (VCCO_14), U1.T11 (VCCO_14), U1.U8 (VCCO_14), U1.U18 (VCCO_14), U1.V15 (VCCO_14); also elsewhere on the board
VGA_B1: U1.B11 (IO_L4N_T0_15); also elsewhere on the board
VGA_B2: U1.B10 (IO_L5P_T0_AD9P_15); also elsewhere on the board
VGA_B3: U1.A10 (IO_L5N_T0_AD9N_15); also elsewhere on the board
VGA_B4: U1.D11 (IO_L6P_T0_15); also elsewhere on the board
VGA_G1: U1.C9 (IO_L2N_T0_AD8N_15); also elsewhere on the board
VGA_G2: U1.B9 (IO_L3P_T0_DQS_AD1P_15); also elsewhere on the board
VGA_G3: U1.A9 (IO_L3N_T0_DQS_AD1N_15); also elsewhere on the board
VGA_G4: U1.C11 (IO_L4P_T0_15); also elsewhere on the board
VGA_HS: U1.M17 (IO_L7N_T1_D10_14); also elsewhere on the board
VGA_R1: U1.D10 (IO_0_15); also elsewhere on the board
VGA_R2: U1.D8 (IO_L1P_T0_AD0P_15); also elsewhere on the board
VGA_R3: U1.C8 (IO_L1N_T0_AD0N_15); also elsewhere on the board
VGA_R4: U1.D9 (IO_L2P_T0_AD8P_15); also elsewhere on the board
VGA_VS: U1.M14 (IO_L8P_T1_D11_14); also elsewhere on the board
